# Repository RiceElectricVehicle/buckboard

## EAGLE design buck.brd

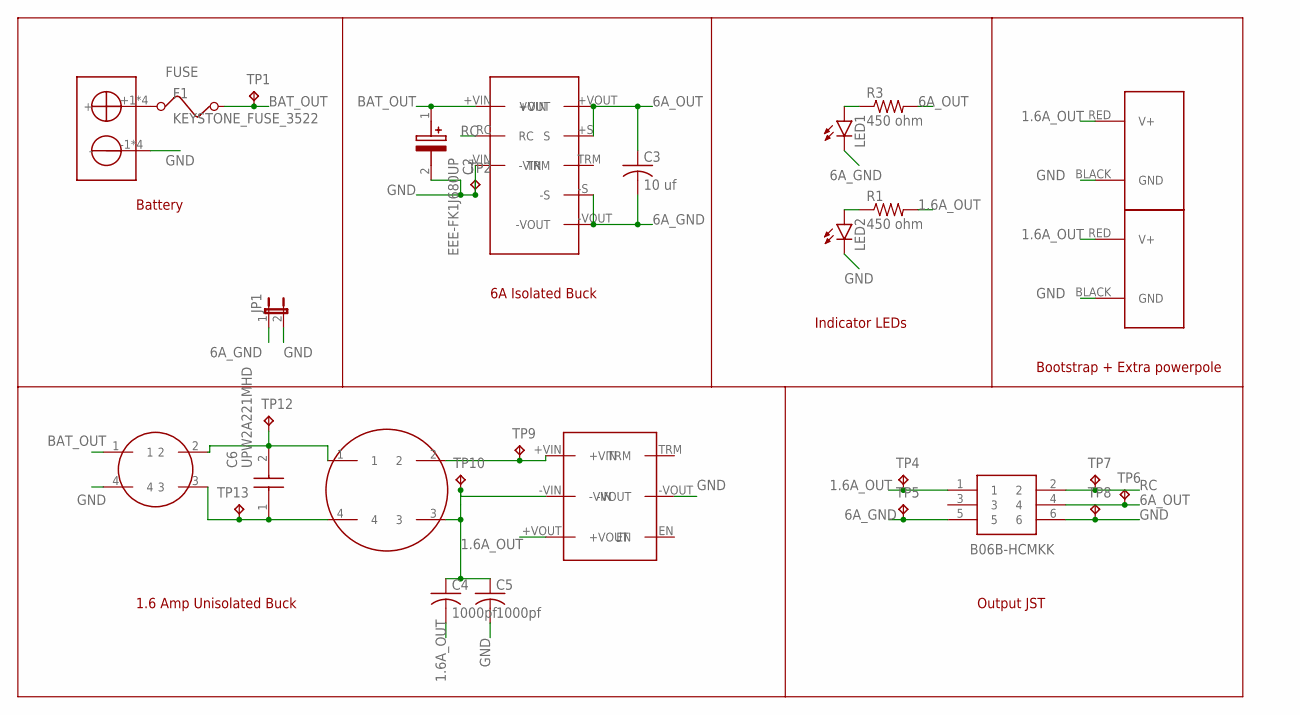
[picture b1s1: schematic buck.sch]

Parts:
BUCK150UH: CMNMODECHOKE150UH
C2: EEE-FK1J680UP; CAPAE830X1050N
C3: 10 uf; C0805
C4, C5: 1000pf; C0805
C6: UPW2A221MHD; CAPPRD550W60D1050H1750
CHOKEME: CMNMODECHOKE1.2MH
F1: KEYSTONE_FUSE_3522
J1: B06B-HCMKK; B06BHCMKK
J2, J3: POWERPOLE_POWER45A_DRILL; POWERPOLE_PAIR_45A_HOLE
JP1: JP1E; JP1
LED1, LED2: LEDCHIP-LED0603; CHIP-LED0603
R1, R3: 450 ohm; R0805
TP1, TP2, TP4, TP5, TP6, TP7, TP8, TP9, TP10, TP12, TP13: TPPAD1-13; P1-13
U$1: 12V6ABUCKCONVERTER
U$2: SB50; MINI-SB-50
U$3: BUCK1.6A

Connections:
1.6A_OUT: C4.2, J1.1, J2.RED (V+), J3.RED (V+), R1.2, TP4.TP, U$3.+VOUT
6A_GND: C3.2, J1.5, JP1.1, LED1.C, TP5.TP, U$1.-S, U$1.-VOUT
6A_OUT: C3.1, J1.4, R3.2, TP6.TP, U$1.+S (S), U$1.+VOUT (VOUT)
BAT_OUT: BUCK150UH.1, C2.1 (+), F1.B1 (2), F1.B2 (2), TP1.TP, U$1.+VIN
FUSE: F1.A1 (1), F1.A2 (1), U$2.+1 (+), U$2.+2 (+), U$2.+3 (+), U$2.+4 (+)
GND: BUCK150UH.4, C2.2 (-), C5.2, J1.6, J2.BLACK (GND), J3.BLACK (GND), JP1.2, LED2.C, TP2.TP, TP8.TP, U$1.-VIN, U$2.-1 (-), U$2.-2 (-), U$2.-3 (-), U$2.-4 (-), U$3.-VOUT
unnamed: BUCK150UH.2, C6.2 (-), CHOKEME.1, TP12.TP
unnamed: BUCK150UH.3, C6.1 (+), CHOKEME.4, TP13.TP
unnamed: CHOKEME.2, TP9.TP, U$3.+VIN
unnamed: C4.1, C5.1, CHOKEME.3, TP10.TP, U$3.-VIN
unnamed: LED2.A, R1.1
unnamed: LED1.A, R3.1
RC: J1.2, TP7.TP, U$1.RC

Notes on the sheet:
1.6 Amp Unisolated Buck
6A Isolated Buck
Battery
Indicator LEDs
Output JST
Bootstrap + Extra powerpole

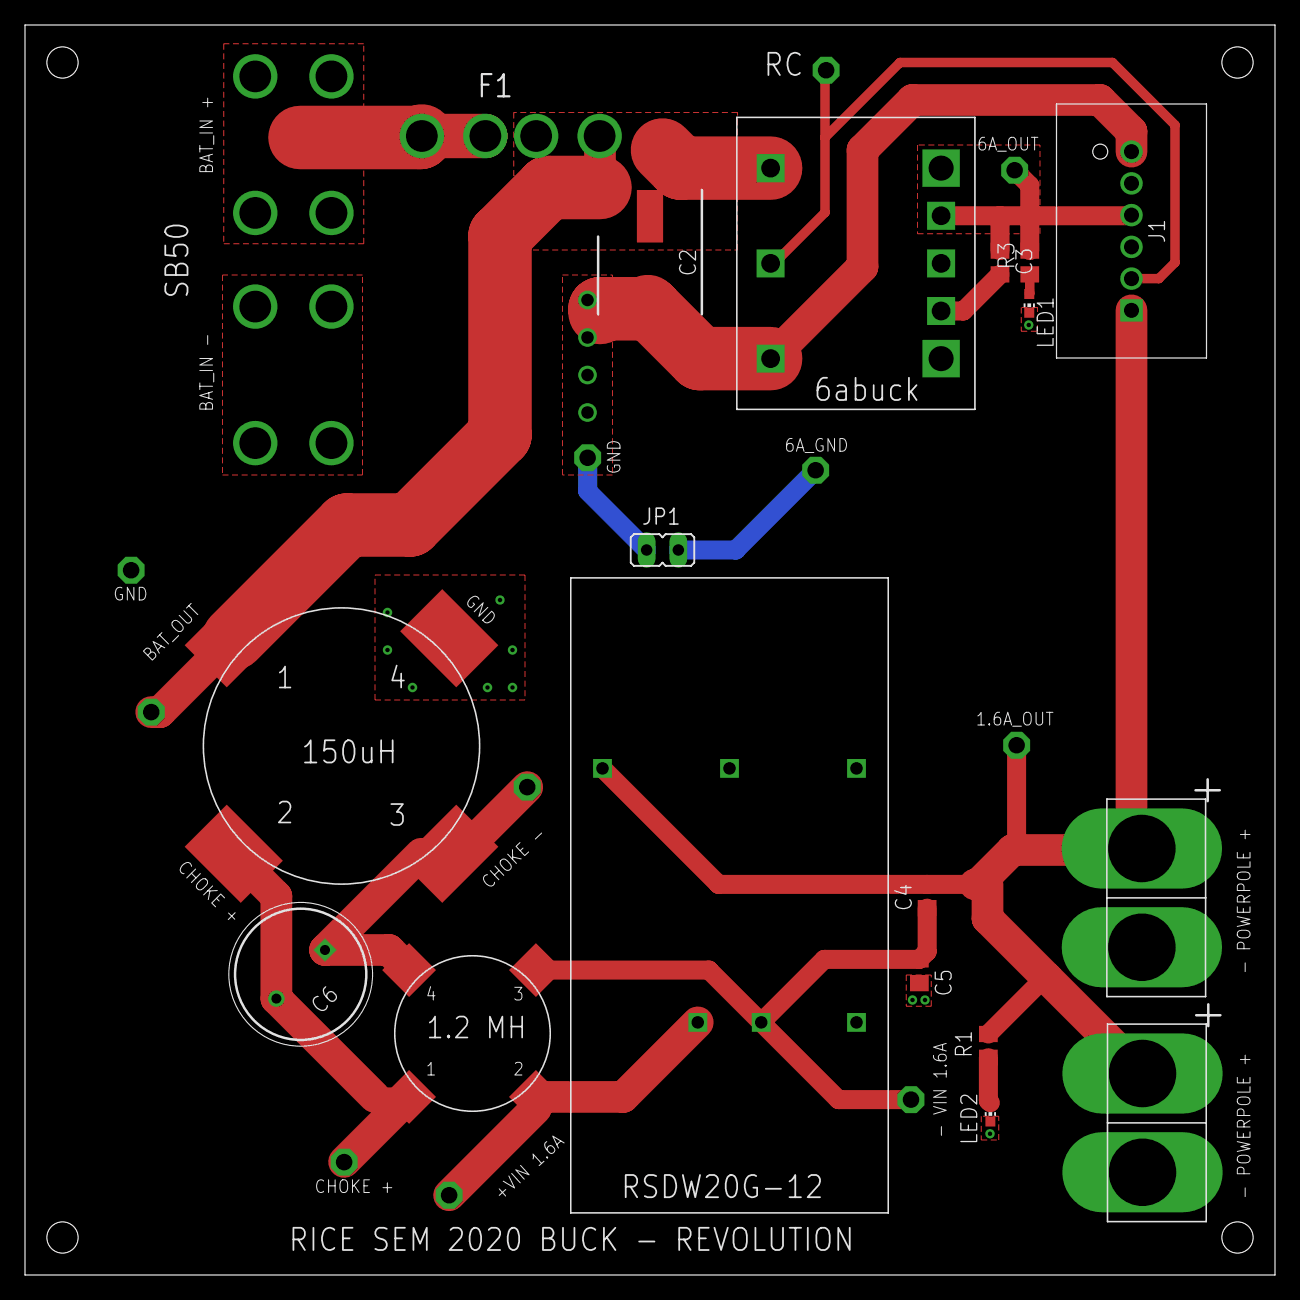
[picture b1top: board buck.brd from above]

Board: 2 copper layers, 100.0 x 100.0 mm, 30 parts (1 on the bottom side), 13 nets.

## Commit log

2020-01-25 fixed pad clearance
2020-01-31 final touches
2020-02-01 Add silkscreen stuff
